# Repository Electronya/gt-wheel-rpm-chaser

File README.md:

# gt-wheel-rpm-chaser
DIY GT Wheel RPM Chaser Board

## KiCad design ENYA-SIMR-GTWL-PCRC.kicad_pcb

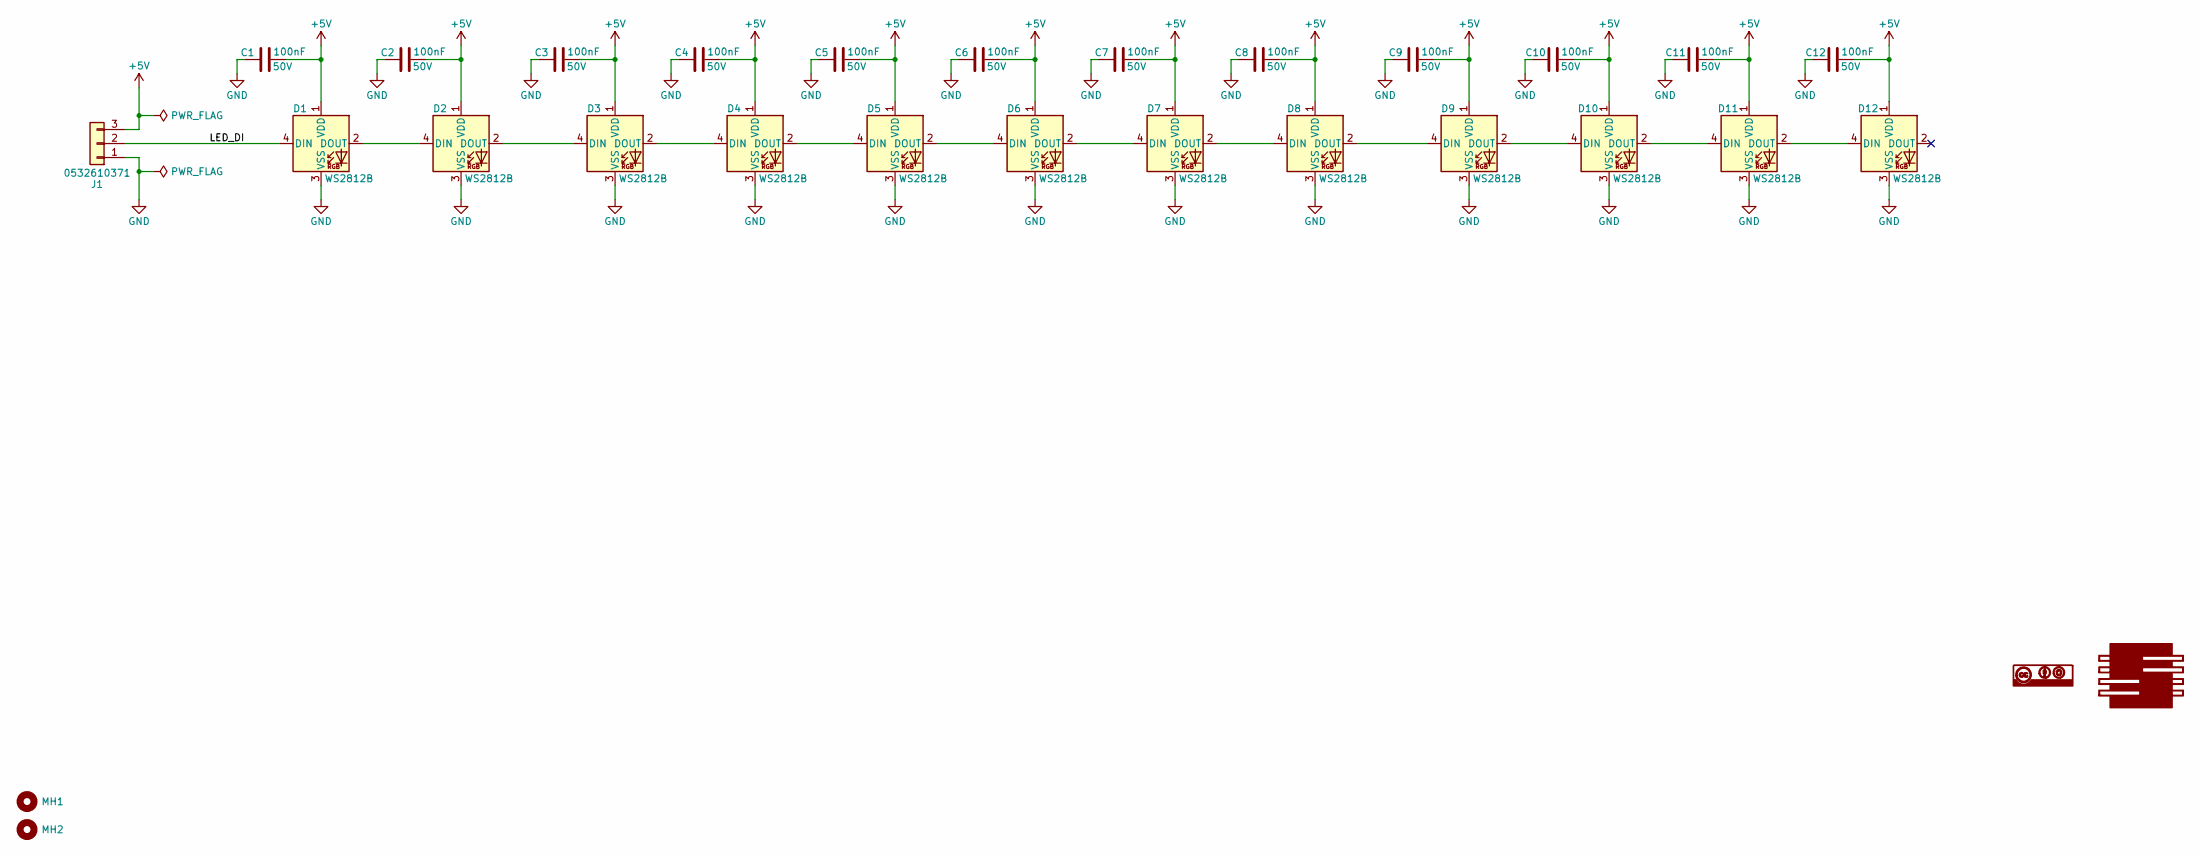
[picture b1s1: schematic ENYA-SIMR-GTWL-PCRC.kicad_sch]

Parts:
C1, C2, C3, C4, C5, C6, C7, C8, C9, C10, C11, C12: 100nF_CER_0603_50V; C_0603_1608Metric; Voltage Rating 50V; Manufacturer Part Number 06033D104MAT2A; Digi-Key Part Number 478-7905-1-ND
D1, D2, D3, D4, D5, D6, D7, D8, D9, D10, D11, D12: WS2812B; LED_WS2812B_PLCC4_5.0x5.0mm_P3.2mm; Manaufacturer Part Numb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 4684; Digi-Key Part Number 1528-4684-ND
G1: Electronya_Logo; Electronya_Logo_12MM
G2: CC-BY-SA_Logo; CC-BY-SA_6MM
J1: PICO_BLADE_1x3_MALE_RA_SMD; PICO_BLADE_53261_1x3_SMD_RA_1.25MM; Manufacturer Part Number 0532610371; Digi-Key Part Number WM7621CT-ND
MH1, MH2: MH-NPLTD-M3; MountingHole_3.2mm_M3_DIN965

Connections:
+5V: C1.2, C2.2, C3.2, C4.2, C5.2, C6.2, C7.2, C8.2, C9.2, C10.2, C11.2, C12.2, D1.1 (VDD), D2.1 (VDD), D3.1 (VDD), D4.1 (VDD), D5.1 (VDD), D6.1 (VDD), D7.1 (VDD), D8.1 (VDD), D9.1 (VDD), D10.1 (VDD), D11.1 (VDD), D12.1 (VDD), J1.3
/LED_DI: D1.4 (DIN), J1.2
GND: C1.1, C2.1, C3.1, C4.1, C5.1, C6.1, C7.1, C8.1, C9.1, C10.1, C11.1, C12.1, D1.3 (VSS), D2.3 (VSS), D3.3 (VSS), D4.3 (VSS), D5.3 (VSS), D6.3 (VSS), D7.3 (VSS), D8.3 (VSS), D9.3 (VSS), D10.3 (VSS), D11.3 (VSS), D12.3 (VSS), J1.1
unnamed: D1.2 (DOUT), D2.4 (DIN)
unnamed: D2.2 (DOUT), D3.4 (DIN)
unnamed: D3.2 (DOUT), D4.4 (DIN)
unnamed: D4.2 (DOUT), D5.4 (DIN)
unnamed: D5.2 (DOUT), D6.4 (DIN)
unnamed: D6.2 (DOUT), D7.4 (DIN)
unnamed: D7.2 (DOUT), D8.4 (DIN)
unnamed: D8.2 (DOUT), D9.4 (DIN)
unnamed: D9.2 (DOUT), D10.4 (DIN)
unnamed: D10.2 (DOUT), D11.4 (DIN)
unnamed: D11.2 (DOUT), D12.4 (DIN)

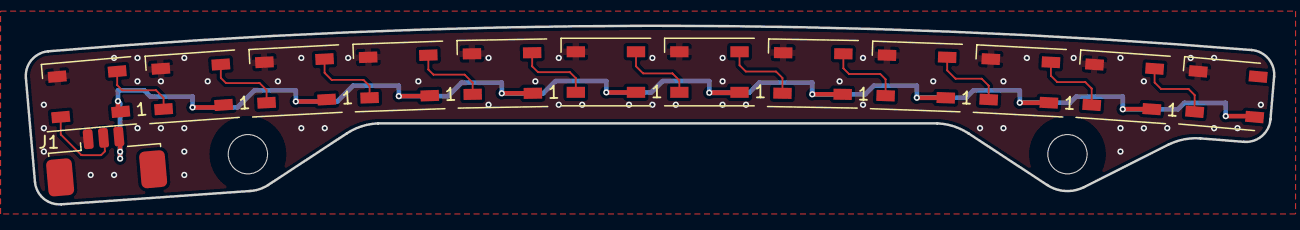
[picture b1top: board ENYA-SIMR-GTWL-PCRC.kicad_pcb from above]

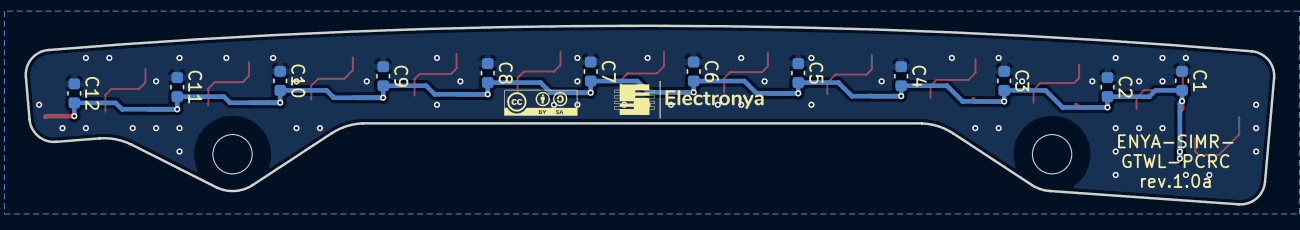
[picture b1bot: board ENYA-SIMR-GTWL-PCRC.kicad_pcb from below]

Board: 2 copper layers, 101.6 x 14.5 mm, 29 parts (14 on the bottom side), 14 nets.

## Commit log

2023-06-30 ready for tag

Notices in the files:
parts and their libraries:
CC-BY-SA, creative common
